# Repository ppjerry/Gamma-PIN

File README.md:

# Gamma-PIN
Semiconductor Radiation Detector

https://hackaday.io/project/159909-gamma-pin-semiconductor-radiation-detector

Disclaimer : all files availible in this repository have been created using official sources of software under licenses I own, the ones owned by the university I attend and carry out my projects under it's patronage and freeware/open source versions of them.

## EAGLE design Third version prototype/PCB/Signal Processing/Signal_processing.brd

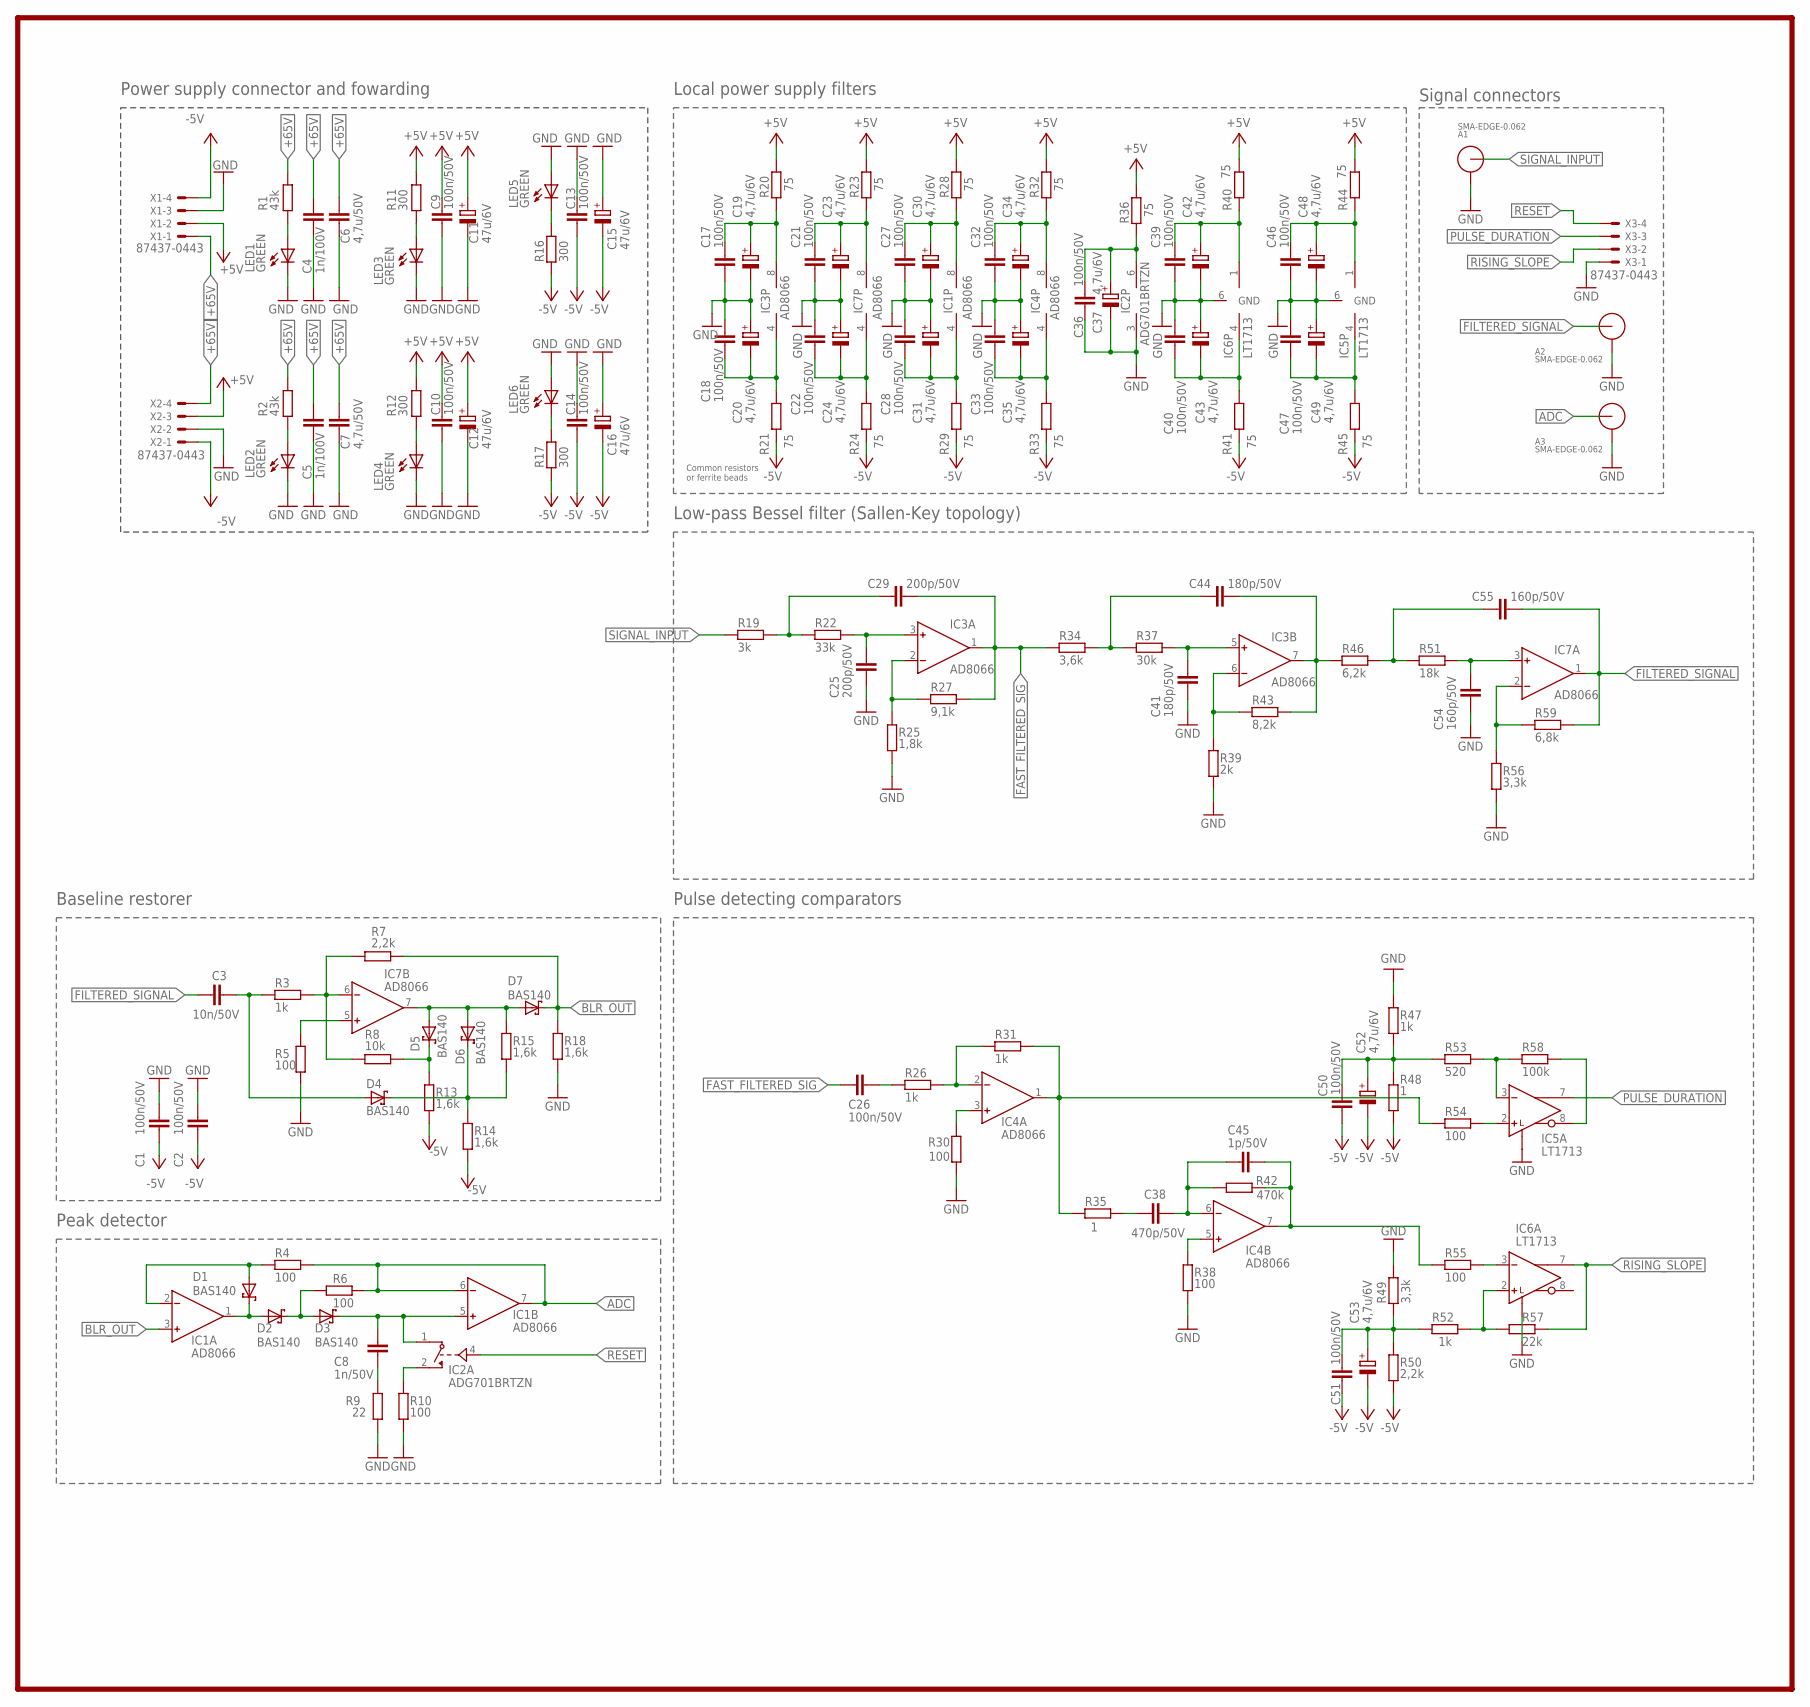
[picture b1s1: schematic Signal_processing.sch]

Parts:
A1, A2, A3: SMA-EDGE-0.062; CONSMA003.062
C1, C2, C9, C10, C13, C14, C17, C18, C21, C22, C26, C27, C28, C32, C33, C36, C39, C40, C46, C47, C50, C51: 100n/50V; C0603
C3: 10n/50V; C0603
C4, C5: 1n/100V; C0603
C6, C7: 4,7u/50V; C1206
C8: 1n/50V; C0603
C11, C12, C15, C16: 47u/6V; SMC_B
C19, C20, C23, C24, C30, C31, C34, C35, C37, C42, C43, C48, C49, C52, C53: 4,7u/6V; SMC_A
C25, C29: 200p/50V; C0603
C38: 470p/50V; C0603
C41, C44: 180p/50V; C0603
C45: 1p/50V; C0603
C54, C55: 160p/50V; C0603
D1, D2, D3, D4, D5, D6, D7: BAS140; SOD2514X100N
IC1, IC3, IC4, IC7: AD8066; MSOP8
IC2: ADG701BRTZN; SOT23-6
IC5, IC6: LT1713; MSOP8
LED1, LED2, LED3, LED4, LED5, LED6: GREEN; CHIPLED_0603
R1, R2: 43k; R0603
R3, R26, R31, R47, R52: 1k; R0603
R4, R5, R6, R10, R30, R38, R54, R55: 100; R0603
R7, R50: 2,2k; R0603
R8: 10k; R0603
R9: 22; R0603
R11, R12, R16, R17: 300; R0603
R13, R14, R15, R18: 1,6k; R0603
R19: 3k; R0603
R20, R21, R23, R24, R28, R29, R32, R33, R36, R40, R41, R44, R45: 75; R0603
R22: 33k; R0603
R25: 1,8k; R0603
R27: 9,1k; R0603
R34: 3,6k; R0603
R35, R48: 1; R0603
R37: 30k; R0603
R39: 2k; R0603
R42: 470k; R0603
R43: 8,2k; R0603
R46: 6,2k; R0603
R49, R56: 3,3k; R0603
R51: 18k; R0603
R53: 520; R0603
R57: 22k; R0603
R58: 100k; R0603
R59: 6,8k; R0603
X1, X2, X3: 87437-0443

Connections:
+5V: C9.2, C10.2, C11.+, C12.+, R11.2, R12.2, R20.1, R23.1, R28.1, R32.1, R36.1, R40.1, R44.1, X1.2, X1.6, X2.3, X2.7
+65V: C4.2, C5.2, C6.1, C7.1, R1.2, R2.2, X1.1, X1.5, X2.4, X2.8
-5V: C1.1, C2.1, C13.1, C14.1, C15.-, C16.-, C50.2, C51.2, C52.-, C53.-, R13.2, R14.2, R16.1, R17.1, R21.2, R24.2, R29.2, R33.2, R41.2, R45.2, R48.2, R50.2, X1.4, X1.8, X2.1, X2.5
ADC: A3.ANT, IC1.6 (IN-), IC1.7 (OUT), R4.2, R6.2
BLR_OUT: D7.K, IC1.3 (IN+), R7.1, R18.1
FAST_FILTERED_SIG: C26.2, C29.1, IC3.1 (OUT), R27.2, R34.1
FILTERED_SIGNAL: A2.ANT, C3.2, C55.1, IC7.1 (OUT), R59.2
GND: A1.GND1, A1.GND2, A1.GND3, A1.GND4, A2.GND1, A2.GND2, A2.GND3, A2.GND4, A3.GND1, A3.GND2, A3.GND3, A3.GND4, C1.2, C2.2, C4.1, C5.1, C6.2, C7.2, C9.1, C10.1, C11.-, C12.-, C13.2, C14.2, C15.+, C16.+, C17.1, C18.2, C19.-, C20.+, C21.1, C22.2, C23.-, C24.+, C25.1, C27.1, C28.2, C30.-, C31.+, C32.1, C33.2, C34.-, C35.+, C36.1, C37.-, C39.1, C40.2, C41.1, C42.-, C43.+, C46.1, C47.2, C48.-, C49.+, C54.1, IC2.3 (V-), IC5.5 (L), IC5.6 (GND), IC6.5 (L), IC6.6 (GND), LED1.C, LED2.C, LED3.C, LED4.C, LED5.A, LED6.A, R5.1, R9.1, R10.1, R18.2, R25.1, R30.1, R38.1, R39.1, R47.1, R49.1, R56.1, X1.3, X1.7, X2.2, X2.6, X3.1, X3.5
unnamed: LED3.A, R11.1
unnamed: LED5.C, R16.2
unnamed: LED2.A, R2.1
unnamed: C18.1, C20.-, IC3.4 (V-), R21.1
unnamed: LED4.A, R12.1
unnamed: C22.1, C24.-, IC7.4 (V-), R24.1
unnamed: LED6.C, R17.2
unnamed: C29.2, R19.2, R22.1
unnamed: C3.1, D4.A, R3.1
unnamed: IC7.6 (IN-), R3.2, R7.2, R8.2
unnamed: D5.A, D6.A, D7.A, IC7.7 (OUT), R15.1
unnamed: D1.K, D2.A, IC1.1 (OUT)
unnamed: C25.2, IC3.3 (IN+), R22.2
unnamed: IC3.2 (IN-), R25.2, R27.1
unnamed: C27.2, C30.+, IC1.8 (V+), R28.2
unnamed: C21.2, C23.+, IC7.8 (V+), R23.2
unnamed: C44.2, R34.2, R37.1
unnamed: D5.K, R8.1, R13.1
unnamed: C28.1, C31.-, IC1.4 (V-), R29.1
unnamed: D4.K, D6.K, R14.1, R15.2
unnamed: D1.A, IC1.2 (IN-), R4.1
unnamed: C55.2, R46.2, R51.1
unnamed: D2.K, D3.A, R6.1
unnamed: IC7.5 (IN+), R5.2
unnamed: LED1.A, R1.1
unnamed: IC4.2 (IN-), R26.2, R31.1
unnamed: C8.1, D3.K, IC1.5 (IN+), IC2.1 (D)
unnamed: C41.2, IC3.5 (IN+), R37.2
unnamed: IC3.6 (IN-), R39.2, R43.1
unnamed: C8.2, R9.2
unnamed: C54.2, IC7.3 (IN+), R51.2
unnamed: C17.2, C19.+, IC3.8 (V+), R20.2
unnamed: C36.2, C37.+, IC2.6 (V+), R36.2
unnamed: IC2.2 (S), R10.2
unnamed: C26.1, R26.1
unnamed: C39.2, C42.+, IC6.1 (V+), R40.2
unnamed: IC4.5 (IN+), R38.2
unnamed: C40.1, C43.-, IC6.4 (V-), R41.1
unnamed: C46.2, C48.+, IC5.1 (V+), R44.2
unnamed: C47.1, C49.-, IC5.4 (V-), R45.1
unnamed: IC7.2 (IN-), R56.2, R59.1
unnamed: IC4.1 (OUT), R31.2, R35.1, R54.1
unnamed: IC4.3 (IN+), R30.2
unnamed: C38.2, R35.2
unnamed: C38.1, C45.2, IC4.6 (IN-), R42.1
unnamed: C45.1, IC4.7 (OUT), R42.2, R55.1
unnamed: IC5.2 (IN+), R54.2
unnamed: IC6.2 (IN+), R52.2, R57.1
unnamed: C51.1, C53.+, R49.2, R50.1, R52.1
unnamed: IC5.3 (IN-), R53.2, R58.1
unnamed: IC5.8 (BOUT), R58.2
unnamed: IC6.3 (IN-), R55.2
unnamed: C32.2, C34.+, IC4.8 (V+), R32.2
unnamed: C50.1, C52.+, R47.2, R48.1, R53.1
unnamed: C33.1, C35.-, IC4.4 (V-), R33.1
unnamed: C44.1, IC3.7 (OUT), R43.2, R46.1
PULSE_DURATION: IC5.7 (OUT), X3.3, X3.7
RESET: IC2.4 (IN), X3.4, X3.8
RISING_SLOPE: IC6.7 (OUT), R57.2, X3.2, X3.6
SIGNAL_INPUT: A1.ANT, R19.1

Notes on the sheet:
Power supply connector and fowarding
Local power supply filters
Common resistors or ferrite beads
Signal connectors
Low-pass Bessel filter (Sallen-Key topology)
Baseline restorer
Peak detector
Pulse detecting comparators

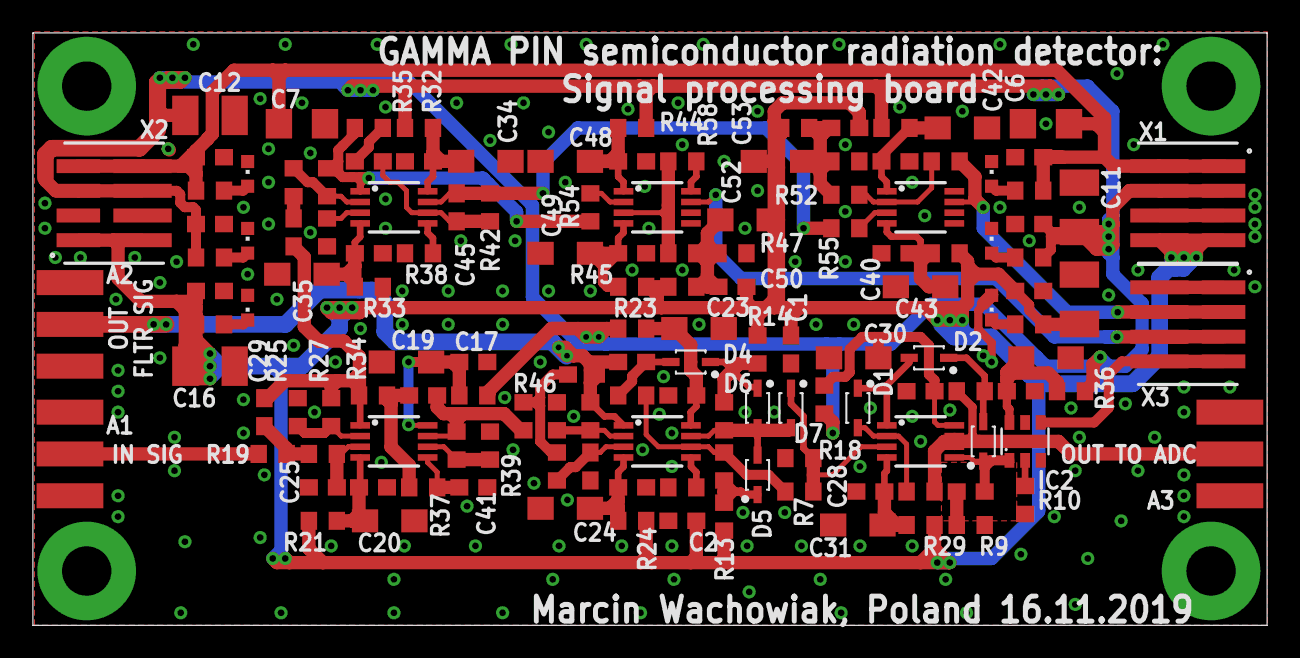
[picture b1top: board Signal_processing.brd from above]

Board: 2 copper layers, 75.0 x 36.0 mm, 140 parts (0 on the bottom side), 68 nets.

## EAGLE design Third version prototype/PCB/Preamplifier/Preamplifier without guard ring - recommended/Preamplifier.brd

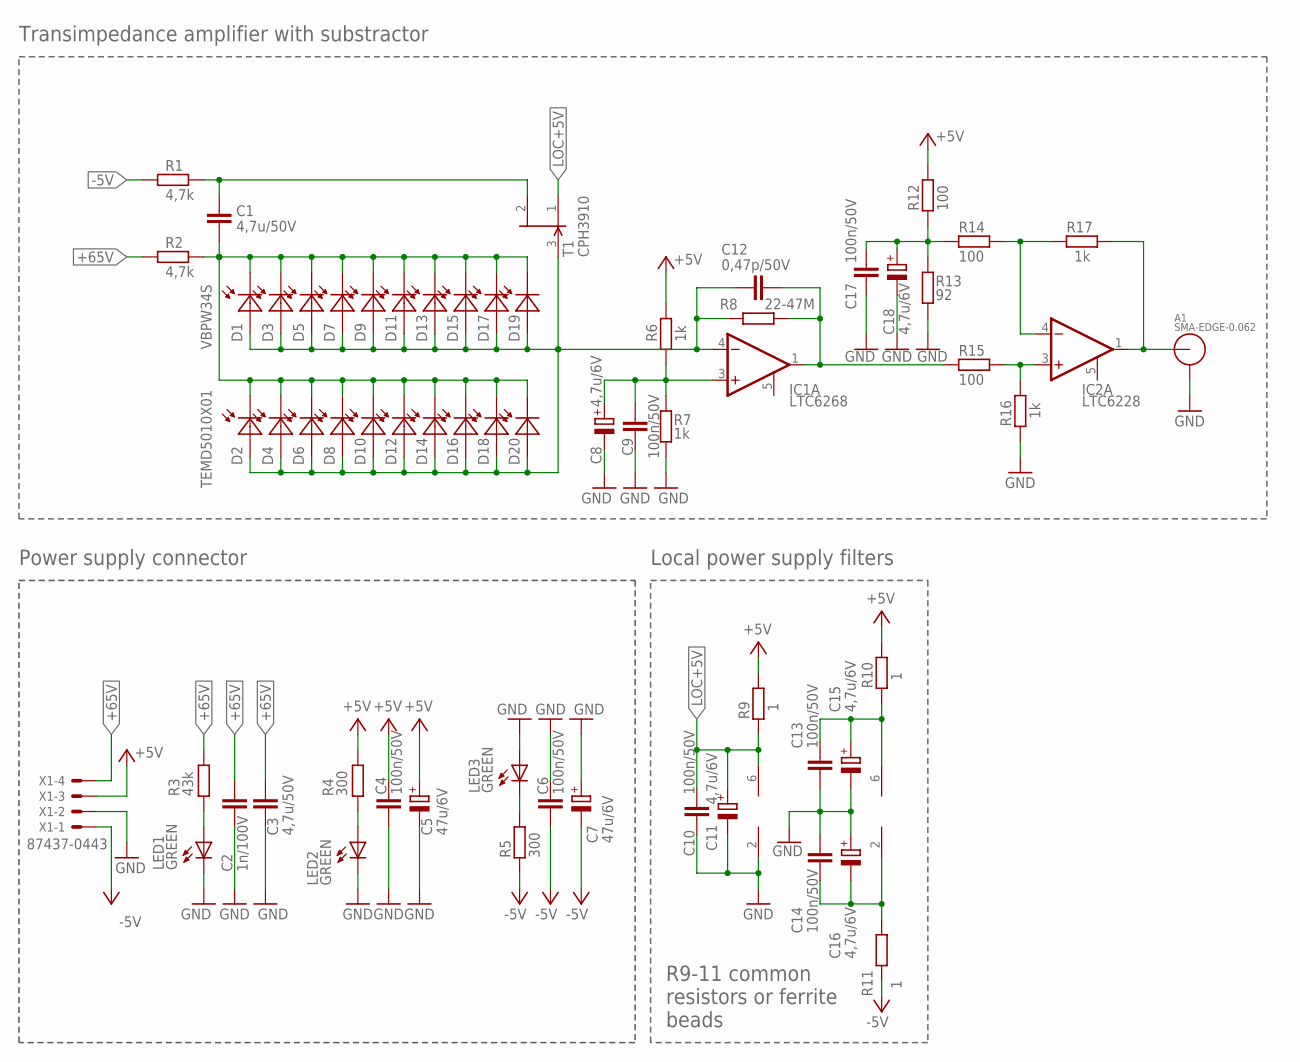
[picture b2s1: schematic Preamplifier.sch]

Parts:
A1: SMA-EDGE-0.062; CONSMA003.062
C1, C3: 4,7u/50V; C1206
C2: 1n/100V; C0603
C4, C6, C9, C10, C13, C14, C17: 100n/50V; C0603
C5, C7: 47u/6V; SMC_B
C8, C11, C15, C16, C18: 4,7u/6V; SMC_A
C12: 0,47p/50V; C0603
D1, D3, D5, D7, D9, D11, D13, D15, D17, D19: VBPW34S; SOD6439X130N
D2, D4, D6, D8, D10, D12, D14, D16, D18, D20: TEMD5010X01; DIODE_TEMD5010
IC1: LTC6268; TSOT23-6
IC2: LTC6228; TSOT23-6
LED1, LED2, LED3: GREEN; CHIPLED_0603
R1, R2: 4,7k; R0603
R3: 43k; R0603
R4, R5: 300; R0603
R6, R7, R16, R17: 1k; R0603
R8: 22-47M; R0603
R9, R10, R11: 1; R0603
R12, R14, R15: 100; R0603
R13: 92; R0603
T1: CPH3910; SOT23
X1: 87437-0443

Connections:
+5V: C4.2, C5.+, R4.2, R6.2, R9.1, R10.1, R12.2, X1.3, X1.7
+65V: C2.2, C3.1, R2.1, R3.2, X1.4, X1.8
-5V: C6.1, C7.-, R1.1, R5.1, R11.2, X1.1, X1.5
GND: A1.GND1, A1.GND2, A1.GND3, A1.GND4, C2.1, C3.2, C4.1, C5.-, C6.2, C7.+, C8.-, C9.1, C10.1, C11.-, C13.1, C14.2, C15.-, C16.+, C17.2, C18.-, IC1.2 (GND), LED1.C, LED2.C, LED3.A, R7.1, R13.1, R16.2, X1.2, X1.6
LOC+5V: C10.2, C11.+, IC1.6 (VDD), R9.2, T1.1 (S)
unnamed: IC2.3 (+IN), R15.1, R16.1
unnamed: C1.2, R1.2, T1.2 (D)
unnamed: C8.+, C9.2, IC1.3 (+IN), R6.1, R7.2
unnamed: C14.1, C16.-, IC2.2 (GND), R11.1
unnamed: A1.ANT, IC2.1 (OUT), R17.2
unnamed: C12.1, IC1.1 (OUT), R8.1, R15.2
unnamed: IC2.4 (-IN), R14.2, R17.1
unnamed: C17.1, C18.+, R12.1, R13.2, R14.1
unnamed: LED1.A, R3.1
unnamed: LED2.A, R4.1
unnamed: LED3.C, R5.2
unnamed: C13.2, C15.+, IC2.6 (VDD), R10.2
unnamed: C12.2, D1.A, D2.2 (A), D3.A, D4.2 (A), D5.A, D6.2 (A), D7.A, D8.2 (A), D9.A, D10.2 (A), D11.A, D12.2 (A), D13.A, D14.2 (A), D15.A, D16.2 (A), D17.A, D18.2 (A), D19.A, D20.2 (A), IC1.4 (-IN), R8.2, T1.3 (G)
unnamed: C1.1, D1.C, D2.1 (C), D3.C, D4.1 (C), D5.C, D6.1 (C), D7.C, D8.1 (C), D9.C, D10.1 (C), D11.C, D12.1 (C), D13.C, D14.1 (C), D15.C, D16.1 (C), D17.C, D18.1 (C), D19.C, D20.1 (C), R2.2

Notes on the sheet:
Transimpedance amplifier with substractor
Power supply connector
Local power supply filters
R9-11 common resistors or ferrite beads

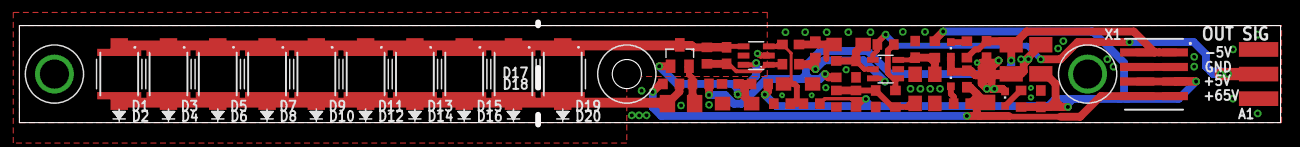
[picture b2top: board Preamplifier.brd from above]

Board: 2 copper layers, 130.0 x 10.0 mm, 63 parts (0 on the bottom side), 19 nets.

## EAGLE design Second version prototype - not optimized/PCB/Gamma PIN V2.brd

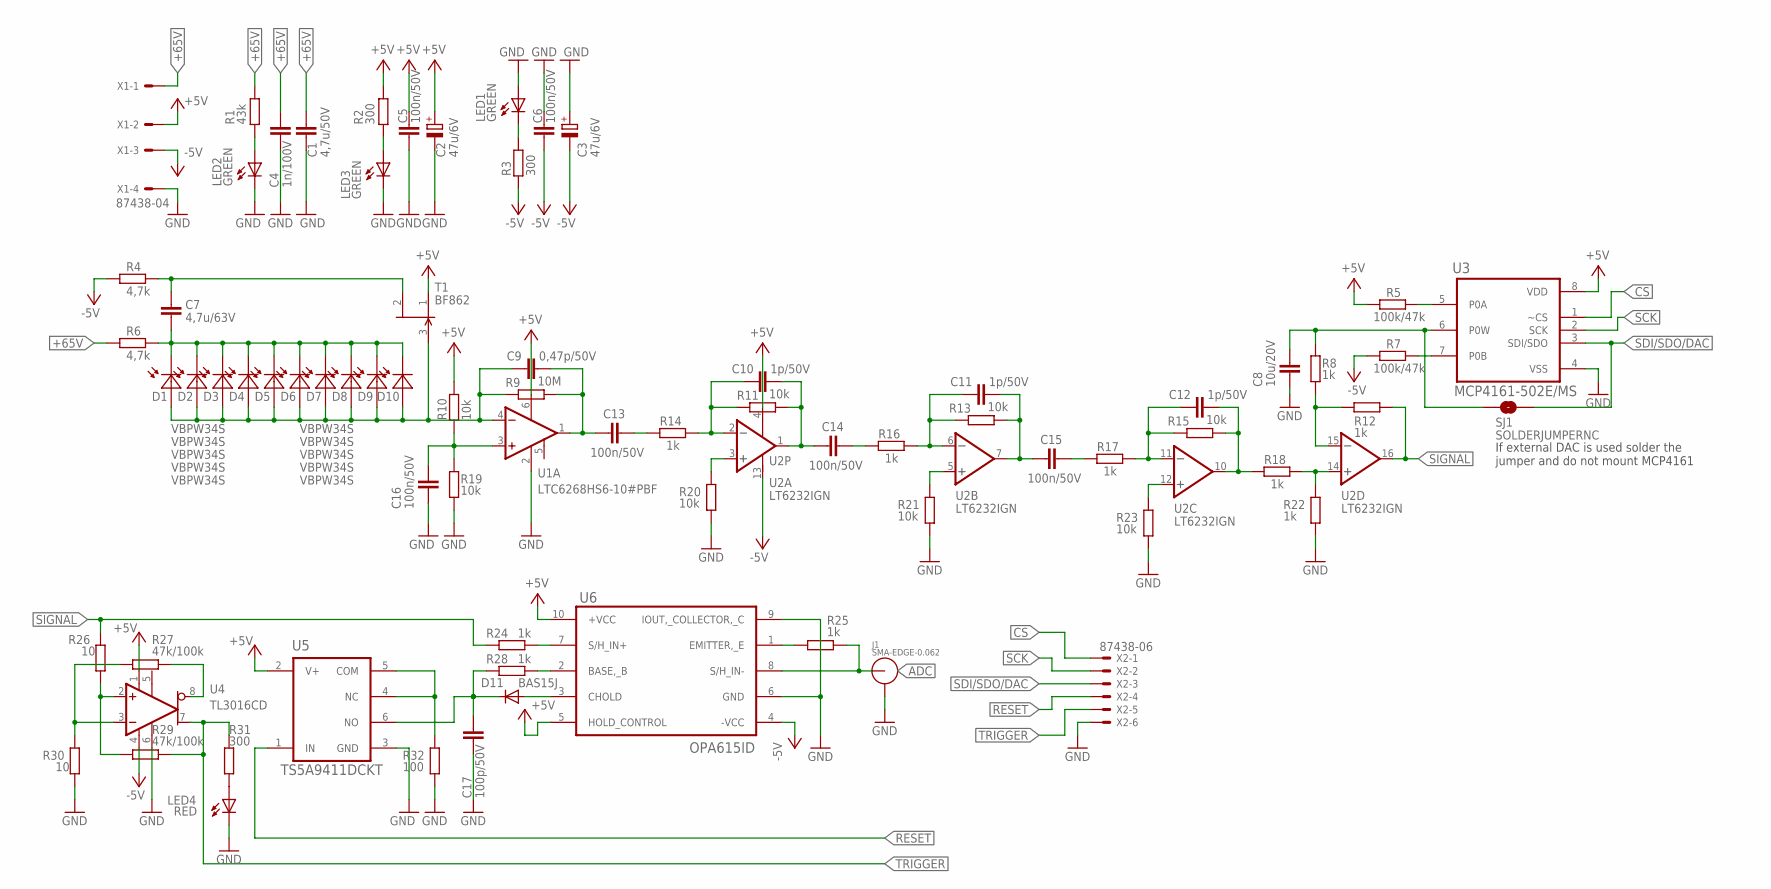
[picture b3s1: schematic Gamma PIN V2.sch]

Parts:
C1: 4,7u/50V; C1206
C2, C3: 47u/6V; SMC_B
C4: 1n/100V; C0603
C5, C6, C13, C14, C15, C16: 100n/50V; C0603
C7: 4,7u/63V; C1206
C8: 10u/20V; C0603
C9: 0,47p/50V; C0603
C10, C11, C12: 1p/50V; C0603
C17: 100p/50V; C0603
D1, D2, D3, D4, D5, D6, D7, D8, D9, D10: VBPW34S; SOD6439X130N
D11: BAS15J; SC79_INFINEON
J1: SMA-EDGE-0.062; CONSMA003.062
LED1, LED2, LED3: GREEN; CHIPLED_0603
LED4: RED; CHIPLED_0603
R1: 43k; R0603
R2, R3, R31: 300; R0603
R4, R6: 4,7k; R0603
R5, R7: 100k/47k; R0603
R8, R12, R14, R16, R17, R18, R22, R24, R25, R28: 1k; R0603
R9: 10M; R0603
R10, R11, R13, R15, R19, R20, R21, R23: 10k; R0603
R26, R30: 10; R0603
R27, R29: 47k/100k; R0603
R32: 100; R0603
SJ1: SOLDERJUMPERNC; SJ_2S_SMALL
T1: BF862; SOT23
U1: LTC6268HS6-10#PBF; TSOT23-6
U2: LT6232IGN; SSOP16
U3: MCP4161-502E/MS; MSOP8
U4: TL3016CD; TSSOP8
U5: TS5A9411DCKT; SOT65P210X110-6N
U6: OPA615ID; MSOP10
X1: 87438-04
X2: 87438-06

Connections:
+5V: C2.+, C5.2, R2.2, R5.1, R10.2, T1.1 (S), U1.6 (VDD), U2.4 (V+), U3.8 (VDD), U4.1 (V+), U5.2 (V+), U6.5 (HOLD_CONTROL), U6.10 (+VCC), X1.2
+65V: C1.1, C4.2, R1.2, R6.1, X1.1
-5V: C3.-, C6.1, R3.1, R4.1, R7.1, U2.13 (V-), U4.4 (V-), U6.4 (-VCC), X1.3
ADC: J1.ANT, R25.1, U6.8 (S/H_IN-)
CS: U3.1 (~CS), X2.1
GND: C1.2, C2.-, C3.+, C4.1, C5.1, C6.2, C8.2, C16.1, C17.1, J1.GND1, J1.GND2, J1.GND3, J1.GND4, LED1.A, LED2.C, LED3.C, LED4.C, R19.1, R20.2, R21.2, R22.2, R23.2, R30.1, R32.2, U1.2 (GND), U3.4 (VSS), U4.6 (GND), U5.3 (GND), U6.6 (GND), U6.9 (IOUT,_COLLECTOR,_C), X1.4, X2.6
unnamed: R8.2, R12.2, U2.15 (-IN)
unnamed: C7.2, R4.2, T1.2 (D)
unnamed: C16.2, R10.1, R19.2, U1.3 (+IN)
unnamed: C7.1, D1.C, D2.C, D3.C, D4.C, D5.C, D6.C, D7.C, D8.C, D9.C, D10.C, R6.2
unnamed: R27.2, R30.2, U4.3 (-IN)
unnamed: C9.2, D1.A, D2.A, D3.A, D4.A, D5.A, D6.A, D7.A, D8.A, D9.A, D10.A, R9.2, T1.3 (G), U1.4 (-IN)
unnamed: C9.1, C13.2, R9.1, U1.1 (OUT)
unnamed: C13.1, R14.2
unnamed: C15.1, R17.2
unnamed: C12.1, R15.1, R18.2, U2.10 (OUT)
unnamed: C14.1, R16.2
unnamed: R20.1, U2.3 (+IN)
unnamed: C10.2, R11.2, R14.1, U2.2 (-IN)
unnamed: C10.1, C14.2, R11.1, U2.1 (OUT)
unnamed: C11.2, R13.2, R16.1, U2.6 (-IN)
unnamed: R18.1, R22.1, U2.14 (+IN)
unnamed: C11.1, C15.2, R13.1, U2.7 (OUT)
unnamed: R21.1, U2.5 (+IN)
unnamed: C12.2, R15.2, R17.1, U2.11 (-IN)
unnamed: C8.1, R8.1, SJ1.1, U3.6 (P0W)
unnamed: R23.1, U2.12 (+IN)
unnamed: R5.2, U3.5 (P0A)
unnamed: R7.2, U3.7 (P0B)
unnamed: R24.1, U6.7 (S/H_IN+)
unnamed: D11.A, U6.3 (CHOLD)
unnamed: R28.1, U6.2 (BASE,_B)
unnamed: LED2.A, R1.1
unnamed: LED4.A, R31.1
unnamed: LED3.A, R2.1
unnamed: LED1.C, R3.2
unnamed: R32.1, U5.4 (NC), U5.5 (COM)
unnamed: R25.2, U6.1 (EMITTER,_E)
unnamed: R27.1, U4.8 (*QOUT)
unnamed: R26.2, R29.2, U4.2 (+IN)
unnamed: C17.2, D11.C, R28.2, U5.6 (NO)
RESET: U5.1 (IN), X2.4
SCK: U3.2 (SCK), X2.2
SDI/SDO/DAC: SJ1.2, U3.3 (SDI/SDO), X2.3
SIGNAL: R12.1, R24.2, R26.1, U2.16 (OUT)
TRIGGER: R29.1, R31.2, U4.7 (QOUT), X2.5

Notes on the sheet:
If external DAC is used solder the jumper and do not mount MCP4161

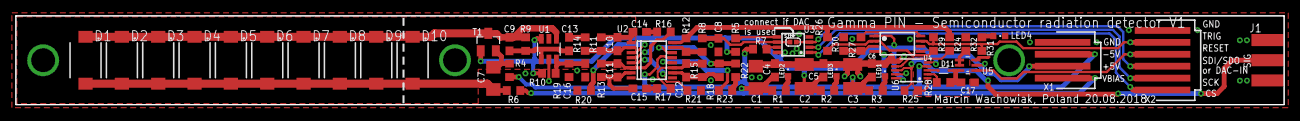
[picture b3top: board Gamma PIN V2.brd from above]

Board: 2 copper layers, 159.6 x 11.2 mm, 75 parts (0 on the bottom side), 46 nets.

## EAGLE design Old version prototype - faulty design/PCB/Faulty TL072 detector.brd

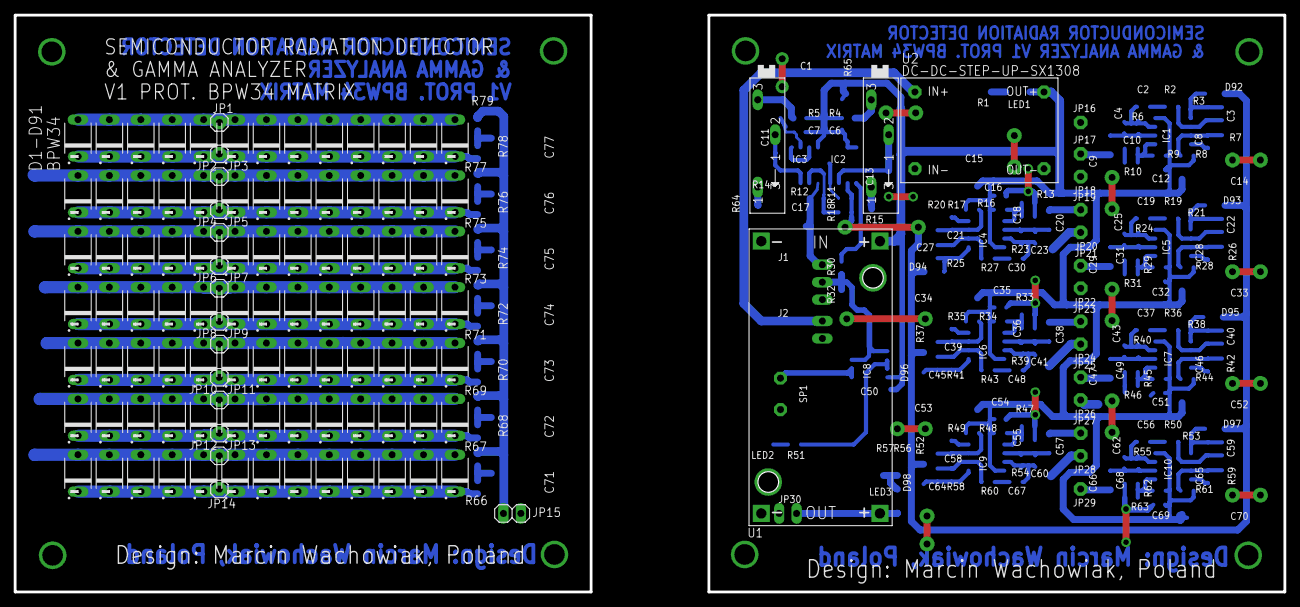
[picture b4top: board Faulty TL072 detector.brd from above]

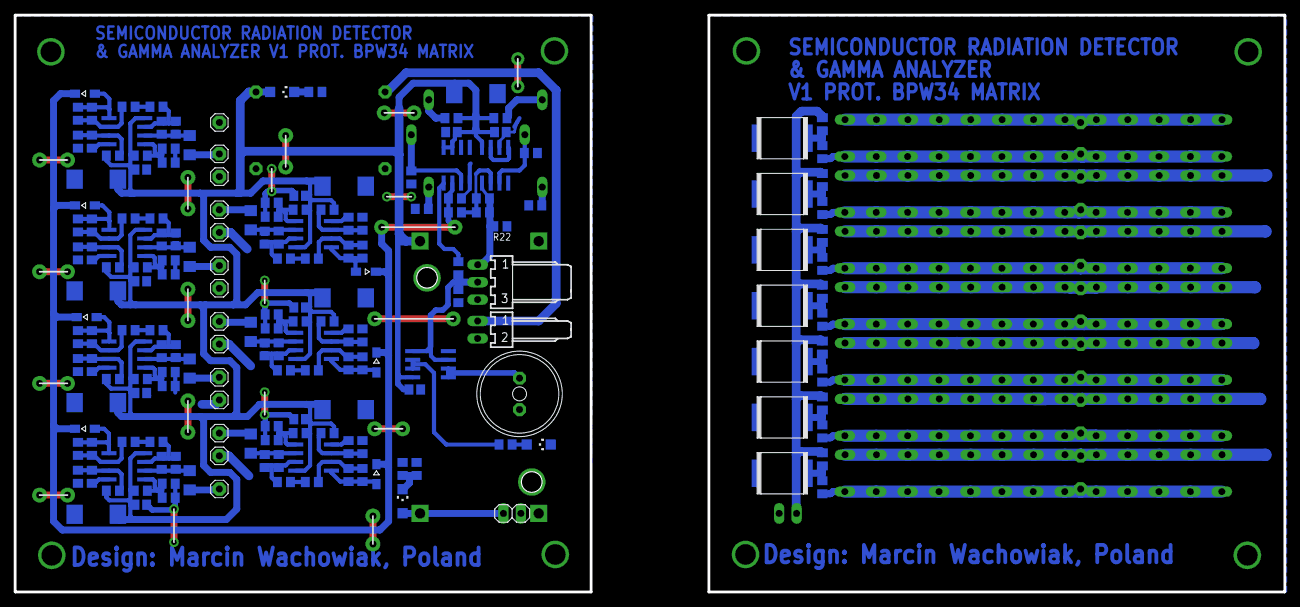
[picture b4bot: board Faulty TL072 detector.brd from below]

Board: 2 copper layers, 184.8 x 83.9 mm, 302 parts (192 on the bottom side), 92 nets.

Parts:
C1, C14, C15, C33, C34, C52, C53, C70: 100u/25V; SMC_D
C2, C19, C30, C37, C48, C56, C67: 22n; C0805
C3, C17, C22, C27, C40, C45, C59, C64: 10p; C0805
C4, C23, C41, C43, C60, C62: 0,5pF; C0603
C5, C24, C26, C42, C44, C61, C63: 0,5/1p; C0805
C6, C7, C8, C10, C11, C12, C13, C16, C18, C21, C28, C31, C32, C35, C36, C39, C46, C49, C50, C51, C54, C55, C58, C65, C68, C69: 100n; C0805
C9, C20, C29, C38, C47, C57, C66: 100n/100V; C1206
C25: 0,5/1p; C0603
C71, C72, C73, C74, C75, C76, C77: 2,2uF/100V; 2824
D1, D2, D3, D4, D5, D6, D7, D8, D9, D10, D11, D12, D13, D14, D15, D16, D17, D18, D19, D20, D21, D22, D23, D24, D25, D26, D27, D28, D29, D30, D31, D32, D33, D34, D35, D36, D37, D38, D39, D40, D41, D42, D43, D44, D45, D46, D47, D48, D49, D50, D51, D52, D53, D54, D55, D56, D57, D58, D59, D60, D61, D62, D63, D64, D65, D66, D67, D68, D69, D70, D71, D72, D73, D74, D75, D76, D77, D78, D79, D80, D81, D82, D83, D84, D85, D86, D87, D88, D89, D90, D91: BPW34; PHODET_BPW34
D92, D93, D94, D95, D96, D97, D98: 1N4448; SOD323-W
IC1, IC4, IC5, IC6, IC7, IC9, IC10: TL072; SO08
IC2: LM311; SO08
IC3, IC8: LM358; SO08
J1: 3pin; 7395-03
J2: 2pin; 7395-02
JP1, JP2, JP3, JP4, JP5, JP6, JP7, JP8, JP9, JP10, JP11, JP12, JP13, JP14, JP16, JP17, JP18, JP19, JP20, JP21, JP22, JP23, JP24, JP25, JP26, JP27, JP28, JP29: 1X01
JP15: GP; 1X02
JP30: 1X02
LED1, LED3: GREEN; CHIPLED_1206
LED2: RED; CHIPLED_1206
R1: 3k; R0805
R2, R4, R5, R14, R15, R19, R27, R36, R43, R50, R60: 1k; R0805
R3, R21, R25, R38, R41, R53, R58: 100k; R0805
R6, R23, R24, R39, R40, R54, R55: 10M; R0805
R7, R8, R9, R10, R11, R13, R16, R17, R18, R20, R22, R26, R28, R29, R31, R33, R34, R35, R37, R42, R44, R45, R46, R47, R48, R49, R52, R59, R61, R62, R63: 10k; R0805
R12: ***; R0805
R30: 1200; R0805
R32: 560; R0805
R51: 470; R0805
R56, R57: 20k; R0805
R64, R65: 100-330 prec; SP19L
R66, R68, R70, R72, R74, R76, R78: 100M; R0805
R67, R69, R71, R73, R75, R77, R79: 1M; M0805
SP1: BUZ; AL11P
U1: DC-DC-STEP-UP-LM2596; DC-DC-STEP-DOWN-LM2596
U2: DC-DC-STEP-UP-SX1308

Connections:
+18V: C1.+, C6.1, C7.1, C12.1, C14.+, C15.+, C16.1, C32.1, C33.+, C34.+, C35.1, C50.2, C51.1, C52.+, C53.+, C54.1, C69.1, C70.+, IC1.8, IC2.7, IC2.8, IC3.8, IC4.8, IC5.8, IC6.8, IC7.8, IC8.8, IC9.8, IC10.8, LED1.A, R4.1, R5.2, R8.1, R9.1, R16.1, R17.1, R28.1, R29.1, R34.1, R35.1, R44.1, R45.1, R48.1, R49.1, R61.1, R62.1, U1.IN+, U2.OUT+
+24V: JP30.1, LED3.A, U1.OUT+
+60: JP15.2, R67.1, R69.1, R71.1, R73.1, R75.1, R77.1, R79.1
A-OUT: C17.2, IC3.1, J1.1, R12.2, R22.2
D-OUT+5V: IC8.3, IC8.5, J1.2, R30.2, R32.1
GND: C1.-, C6.2, C7.2, C8.1, C10.1, C11.1, C12.2, C13.2, C14.-, C15.-, C16.2, C18.1, C21.1, C28.1, C31.1, C32.2, C33.-, C34.-, C35.2, C36.1, C39.1, C46.1, C49.1, C50.1, C51.2, C52.-, C53.-, C54.2, C55.1, C58.1, C65.1, C68.1, C69.2, C70.-, C71.2, C72.2, C73.2, C74.2, C75.2, C76.2, C77.2, D1.A, D2.A, D3.A, D4.A, D5.A, D6.A, D7.A, D8.A, D9.A, D10.A, D11.A, D12.A, D13.A, D14.A, D15.A, D16.A, D17.A, D18.A, D19.A, D20.A, D21.A, D22.A, D23.A, D24.A, D25.A, D26.A, D27.A, D28.A, D29.A, D30.A, D31.A, D32.A, D33.A, D34.A, D35.A, D36.A, D37.A, D38.A, D39.A, D40.A, D41.A, D42.A, D43.A, D44.A, D45.A, D46.A, D47.A, D48.A, D49.A, D50.A, D51.A, D52.A, D53.A, D54.A, D55.A, D56.A, D57.A, D58.A, D59.A, D60.A, D61.A, D62.A, D63.A, D64.A, D65.A, D66.A, D67.A, D68.A, D69.A, D70.A, D71.A, D72.A, D73.A, D74.A, D75.A, D76.A, D77.A, D78.A, D79.A, D80.A, D81.A, D82.A, D83.A, D84.A, D85.A, D86.A, D87.A, D88.A, D89.A, D90.A, D91.A, IC1.4, IC2.4, IC3.4, IC3.6, IC4.4, IC5.4, IC6.4, IC7.4, IC8.4, IC9.4, IC10.4, J1.3, J2.2, JP1.1, JP3.1, JP5.1, JP7.1, JP9.1, JP11.1, JP13.1, JP15.1, JP16.1, JP18.1, JP20.1, JP22.1, JP24.1, JP26.1, JP28.1, JP30.2, LED2.C, R1.2, R7.2, R10.2, R11.2, R13.2, R14.1, R15.2, R20.2, R22.1, R26.2, R31.2, R32.2, R33.2, R37.2, R42.2, R46.2, R47.2, R52.2, R56.2, R57.2, R59.2, R63.2, SP1.-, U1.IN-, U1.OUT-, U2.IN-, U2.OUT-
unnamed: C10.2, IC1.5, R9.2, R10.1
unnamed: C2.1, C4.1, C5.1, IC1.7, R6.1
unnamed: J2.1, U2.IN+
unnamed: C77.1, R78.1, R79.2
unnamed: C8.2, IC1.3, R7.1, R8.2
unnamed: C2.2, R2.2
unnamed: C4.2, C5.2, C9.2, IC1.6, R6.2
unnamed: C3.2, IC1.2, R2.1, R3.2
unnamed: C3.1, D92.A, IC1.1, R3.1
unnamed: D92.C, D93.C, D94.C, D95.C, D96.C, D97.C, D98.C, IC2.2, R11.1, R18.1
unnamed: C76.1, R76.1, R77.2
unnamed: C75.1, R74.1, R75.2
unnamed: C74.1, R72.1, R73.2
unnamed: C73.1, R70.1, R71.2
unnamed: C72.1, R68.1, R69.2
unnamed: C71.1, R66.1, R67.2
unnamed: IC2.1, R30.1
unnamed: C17.1, IC3.2, R12.1, R18.2
unnamed: C13.1, IC2.3, R65.S
unnamed: R4.2, R65.E
unnamed: R15.1, R65.A
unnamed: C25.2, C26.2, C29.2, IC5.6, R24.2
unnamed: R5.1, R64.E
unnamed: R14.2, R64.A
unnamed: C11.2, IC3.3, R64.S
unnamed: LED1.C, R1.1
unnamed: C31.2, IC5.5, R29.2, R31.1
unnamed: LED3.C, R56.1, R57.1
unnamed: C19.1, C25.1, C26.1, IC5.7, R24.1
unnamed: C19.2, R19.2
unnamed: C22.2, IC5.2, R19.1, R21.2
unnamed: C22.1, D93.A, IC5.1, R21.1
unnamed: C28.2, IC5.3, R26.1, R28.2
unnamed: C38.2, C41.2, C42.2, IC6.6, R39.2
unnamed: C36.2, IC6.5, R33.1, R34.2
unnamed: C43.2, C44.2, C47.2, IC7.6, R40.2
unnamed: C49.2, IC7.5, R45.2, R46.1
unnamed: C37.1, C43.1, C44.1, IC7.7, R40.1
unnamed: C37.2, R36.2
unnamed: C40.2, IC7.2, R36.1, R38.2
unnamed: C40.1, D95.A, IC7.1, R38.1
unnamed: C46.2, IC7.3, R42.1, R44.2
unnamed: C41.1, C42.1, C48.1, IC6.7, R39.1
unnamed: C48.2, R43.2
unnamed: C62.2, C63.2, C66.2, IC10.6, R55.2
unnamed: C68.2, IC10.5, R62.2, R63.1
unnamed: C56.1, C62.1, C63.1, IC10.7, R55.1
unnamed: C56.2, R50.2
unnamed: C59.2, IC10.2, R50.1, R53.2
unnamed: C59.1, D97.A, IC10.1, R53.1
unnamed: C65.2, IC10.3, R59.1, R61.2
unnamed: C45.2, IC6.2, R41.2, R43.1
unnamed: C45.1, D96.A, IC6.1, R41.1
unnamed: C20.2, C23.2, C24.2, IC4.6, R23.2
unnamed: C18.2, IC4.5, R13.1, R16.2
unnamed: C23.1, C24.1, C30.1, IC4.7, R23.1
unnamed: C30.2, R27.2
unnamed: C27.2, IC4.2, R25.2, R27.1
unnamed: C27.1, D94.A, IC4.1, R25.1
unnamed: C21.2, IC4.3, R17.2, R20.1
unnamed: C39.2, IC6.3, R35.2, R37.1
unnamed: C57.2, C60.2, C61.2, IC9.6, R54.2
unnamed: C55.2, IC9.5, R47.1, R48.2
unnamed: C60.1, C61.1, C67.1, IC9.7, R54.1
unnamed: C67.2, R60.2
unnamed: C64.2, IC9.2, R58.2, R60.1
unnamed: C64.1, D98.A, IC9.1, R58.1
unnamed: C58.2, IC9.3, R49.2, R52.1
unnamed: IC8.1, IC8.2, SP1.+
unnamed: IC8.6, IC8.7, R51.2
OUT1: D27.C, D28.C, D29.C, D30.C, D31.C, D32.C, D33.C, D34.C, D35.C, D36.C, D37.C, D38.C, D39.C, JP6.1, R74.2
OUT3: D79.C, D80.C, D81.C, D82.C, D83.C, D84.C, D85.C, D86.C, D87.C, D88.C, D89.C, D90.C, D91.C, JP14.1, R66.2
OUT4: D1.C, D2.C, D3.C, D4.C, D5.C, D6.C, D7.C, D8.C, D9.C, D10.C, D11.C, D12.C, D13.C, JP2.1, R78.2
OUT5: D14.C, D15.C, D16.C, D17.C, D18.C, D19.C, D20.C, D21.C, D22.C, D23.C, D24.C, D25.C, D26.C, JP4.1, R76.2
OUT9: D40.C, D41.C, D42.C, D43.C, D44.C, D45.C, D46.C, D47.C, D48.C, D49.C, D50.C, D51.C, D52.C, JP8.1, R72.2
OUT10: C9.1, JP17.1
OUT12: C20.1, JP19.1
OUT13: C66.1, JP29.1
OUT14: C29.1, JP21.1
OUT15: C38.1, JP23.1
OUT16: C47.1, JP25.1
OUT17: C57.1, JP27.1
OUT21: D53.C, D54.C, D55.C, D56.C, D57.C, D58.C, D59.C, D60.C, D61.C, D62.C, D63.C, D64.C, D65.C, JP10.1, R70.2
OUT22: D66.C, D67.C, D68.C, D69.C, D70.C, D71.C, D72.C, D73.C, D74.C, D75.C, D76.C, D77.C, D78.C, JP12.1, R68.2
S$1: IC3.5, IC3.7
S$2: LED2.A, R51.1

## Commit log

2018-07-22 Add files via upload
    Old prototype of detector based on common TL072 amplifiers.
2018-07-22 Add files via upload
    Old version of the detector using common TL072 amplifiers.
2018-07-22 Add files via upload
    Old version prototype with array of 7 individual sensing rows of BPW34 with TL072. Generating negative output signal which is blocked by diode stopping the signal. The problem lays in adding of the s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
2018-07-28 Create old version protorype
2018-07-28 Create 1
2018-07-29 Added LTspice simulation files
2018-07-29 Added sch/pcb files
2018-07-29 Added Eagle sch/brd files
2018-08-01 Create New version prototype
2019-07-10 Create First version prototype - faulty design
2019-07-10 Reupload
2020-02-16 Uploaded third version brd, sch, sim files
2020-02-16 Removed guard ring due to ocurring shorts and adjusted supply rail resistors
2020-02-16 Added gerbers
2020-02-16 Added partialy exposed guard ring design
2020-02-23 Updated terms of use
2020-02-23 Added MAV screenshots

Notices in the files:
parts and their libraries:
diy-modules: Released under the Creative Commons Attribution 4.0 International License: http://creativecommons.org/licenses/by/4.0
NXP_60_26022015: This library may be distributed and adapted freely for any purpose, as long as NXP is credited and any new creation is licensed under the same terms.
